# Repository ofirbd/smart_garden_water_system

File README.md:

# Smart Garden Water System

## Project Overview

This repository contains the software and hardware design for a smart garden system designed to automate watering, monitor water consumption, and track environmental conditions (temperature and humidity). The system leverages an ESP32 microcontroller for edge device control and a Raspberry Pi as a central hub, all controllable via a dedicated mobile application.

Built upon prior experience with ESP32 and MQTT, this project aims to create a robust, scalable, and user-friendly solution for efficient garden management.

## Key Features

* **Automated Watering:** Schedule-based watering for up to 3 individual garden zones.
* **Manual Control:** On-demand opening and closing of each water valve via the mobile app.
* **Water Usage Monitoring:** Real-time and historical tracking of total and session water consumption from a single water meter.
* **Environmental Monitoring:** Live readings and historical data for garden temperature and humidity.
* **System Status:** Real-time feedback on valve states, device connectivity, and battery levels.
* **Notifications:** Alerts for critical events (e.g., low battery, potential issues).
* **User-Friendly Mobile App:** Intuitive interface for control, monitoring, and configuration.

## System Architecture

The system follows a star-topology with a central Raspberry Pi hub communicating with a single, powerful ESP32 edge device.

```
+-------------------+             +-----------------------+
|                   |             |                       |
| Mobile Application| <---------> | Central Control Unit  |
| (Android/iOS)     | (MQTT/HTTP) | (Raspberry Pi)        |
|                   |             | - MQTT Broker         |
+-------------------+             | - Data Storage        |
| - API/Web Server      |
+-----------+-----------+
|
| MQTT
|
+-----------+-----------+
|                       |
| Combined Smart Water  |
| Unit (ESP32)          |
| - 3x Valve Actuation  |
| - 1x Water Flow Sensor|
| - Temp/Hum Sensors    |
| - Status Reporting    |
| - Data Reporting      |
| - Battery/Power       |
+-----------------------+
```

## Components

### 1. Combined Smart Water Unit (ESP32 Firmware & Hardware)

This single ESP32 board manages all direct interactions with the garden.

* **Microcontroller:** ESP32 (e.g., ESP32-WROOM-32 or similar, ensuring sufficient GPIOs).
* **Valve Actuators:** 3 x Latching Solenoid Valves (recommended for their minimal power consumption) with appropriate driver circuits (e.g., MOSFET H-bridge for polarity switching).
* **Water Flow Sensor:** 1 x Hall-effect flow sensor (e.g., YF-S201C or equivalent), connected to an interrupt-capable GPIO.
* **Temperature/Humidity Sensor:** [Specify your chosen sensor, e.g., BME280 (I2C) or DHT22 (1-wire)].
* **Power Supply:** Designed for outdoor deployment, likely battery-powered (e.g., 18650 Li-ion cells) with a robust charging circuit (e.g., solar panel + charge controller) and efficient voltage regulation. Alternatively, mains power if available.
* **Enclosure:** IP65/IP67 rated waterproof enclosure to protect electronics from elements.
* **Firmware:** Developed in C++ using the [ESP-IDF framework / Arduino IDE].

### 2. Central Control Unit (Raspberry Pi Software & Hardware)

The brain of the system, handling data, scheduling, and communication with the mobile app.

* **Hardware:** Raspberry Pi [Specify model, e.g., 3B+, 4, or 5].
* **Operating System:** Raspberry Pi OS (formerly Raspbian).
* **MQTT Broker:** Mosquitto (for reliable message queuing between devices).
* **Database:** SQLite (chosen for its lightweight nature, ease of setup, and suitability for the project's data scale).
    * Stores sensor readings, valve states, schedules, and device information.
* **Backend Application/API:** A custom application written in [Python (e.g., Flask/FastAPI), Node.js (e.g., Express), or Go].
    * Listens to MQTT messages, stores data in SQLite, implements scheduling logic, and exposes a RESTful API for the mobile application.
* **Web Tool (Optional but Recommended):** [Specify your chosen tool, e.g., Home Assistant, Node-RED, or ThingsBoard].
    * Provides a ready-made web interface for dashboards, charts, and rule-based automation, significantly reducing development time for the UI.

### 3. Mobile Application

The primary user interface for controlling and monitoring the garden from anywhere.

* **Platform:** Compatible with Android and/or iOS devices.
* **Technology Stack:** [Specify, e.g., React Native, Flutter, Native Kotlin/Swift].
* **Functionality:**
    * Dashboard view with current status and summarized data.
    * Individual valve control (on/off).
    * Display of current and historical water meter readings.
    * Display of current and historical temperature and humidity data.
    * Creation, editing, and deletion of watering schedules per valve.
    * System configuration settings.

## Detailed System Description and Requirements

For an in-depth understanding of the system's complete architecture, detailed hardware and software requirements for each component, precise communication protocols, and in-depth design considerations, please refer to the dedicated **[system_requirements.md](./01-docs/system_requirements.md)** and  **[system_detailed_design.md](./01-docs/system_detailed_design.md)** documents. These comprehensive documents also outlines potential future enhancements and specific implementation details.

## Setup & Installation

Follow these steps to get your Smart Garden Water System up and running:

### 1. Raspberry Pi (Central Control Unit) Setup

1.  **Prepare Raspberry Pi OS:**
    * Download and flash the latest Raspberry Pi OS (Lite or Desktop, depending on your preference) onto a microSD card using [Raspberry Pi Imager](https://www.raspberrypi.com/software/).
    * Enable SSH for remote access.
2.  **Install Mosquitto MQTT Broker:**
    
    ```bash
    sudo apt update
    sudo apt install mosquitto mosquitto-clients
    sudo systemctl enable mosquitto
    sudo systemctl start mosquitto
    # For security, consider configuring MQTT users and passwords (refer to Mosquitto docs).
    ```
3.  **Setup Backend Application / Web Tool:**
    * **If using a custom backend:**
        ```bash
        git clone [Your_Repository_URL]
        cd [Your_Repository_Name]/backend/
        # Install Python dependencies (example for Python)
        pip install -r requirements.txt
        # Run the backend application (e.g., using Gunicorn for production)
        python app.py
        ```
    * **If using Home Assistant:** Follow the official installation guide (e.g., Home Assistant OS, Container, or Supervised for Raspberry Pi). Ensure MQTT integration is configured to connect to your Mosquitto broker.
    * **If using Node-RED:** Install via the recommended script for Raspberry Pi: `bash <(curl -sL https://raw.githubusercontent.com/node-red/linux-installers/master/deb/update-nodejs-and-nodered)` Then install necessary nodes (e.g., `node-red-contrib-mqtt`, `node-red-node-sqlite`).
    * **If using ThingsBoard:** Follow the official ThingsBoard Community Edition installation guide for Raspberry Pi (Docker is often the easiest).

### 2. ESP32 (Smart Water Unit) Firmware

1.  **Set up Development Environment:**
    * Install either [ESP-IDF](https://docs.espressif.com/projects/esp-idf/en/latest/esp32/get-started/index.html) or [Arduino IDE with ESP32 board support](https://docs.espressif.com/projects/arduino-esp32/en/latest/installing.html).
2.  **Clone Firmware Repository:**
    ```bash
    git clone [Your_Repository_URL]
    cd [Your_Repository_Name]/esp32_firmware/
    ```
3.  **Configure Network & MQTT:**
    * Open the firmware project in your IDE.
    * Locate and edit the configuration file (e.g., `src/config.h`, `secrets.h`, or similar) to enter your Wi-Fi SSID, password, and the IP address/hostname of your Raspberry Pi's MQTT broker.
4.  **Compile and Upload:**
    * Compile the firmware and upload it to your ESP32 board. Ensure correct board and serial port are selected in your IDE.

### 3. Mobile Application

1.  **Clone Mobile App Repository:**
    ```bash
    git clone [Your_Mobile_App_Repository_URL]
    cd [Your_Mobile_App_Repository_Name]
    ```
2.  **Install Dependencies:**
    * For React Native: `npm install` or `yarn install`
    * For Flutter: `flutter pub get`
    * Follow specific instructions for your chosen framework.
3.  **Configure API Endpoint:**
    * In the app's source code, update the backend API base URL to point to your Raspberry Pi's IP address (e.g., `http://[Raspberry_Pi_IP_Address]:[Backend_Port]`).
4.  **Build and Run:**
    * Run the app on an emulator or a physical device:
        * React Native: `npm run android` / `npm run ios`
        * Flutter: `flutter run`
    * Alternatively, build release APK/IPA files for direct installation.

## Usage

1.  **Power On Devices:** Ensure your Raspberry Pi and the ESP32 Smart Water Unit are powered on and connected to your local network.
2.  **Verify MQTT Communication:** Monitor the Mosquitto broker logs (`sudo tail -f /var/log/mosquitto/mosquitto.log`) to confirm the ESP32 is publishing data and subscribing correctly.
3.  **Access Interface:**
    * **Mobile App:** Launch the "Smart Garden Water System" app on your smartphone.
    * **Web Tool:** Open your web browser and navigate to `http://[Raspberry_Pi_IP_Address]:[Web_Tool_Port]` (e.g., `http://192.168.1.100:8123` for Home Assistant, `http://192.168.1.100:1880` for Node-RED, `http://192.168.1.100:8080` for ThingsBoard).
4.  **Control & Monitor:**
    * Use the interface to manually open or close individual water valves.
    * View real-time and historical graphs for water flow, total volume, temperature, and humidity.
    * Create and manage custom watering schedules for your garden zones.
    * Check the battery status and overall health of your ESP32 unit.

## License

This project is open-source and distributed under the MIT License. See the `LICENSE` file for more details.

---

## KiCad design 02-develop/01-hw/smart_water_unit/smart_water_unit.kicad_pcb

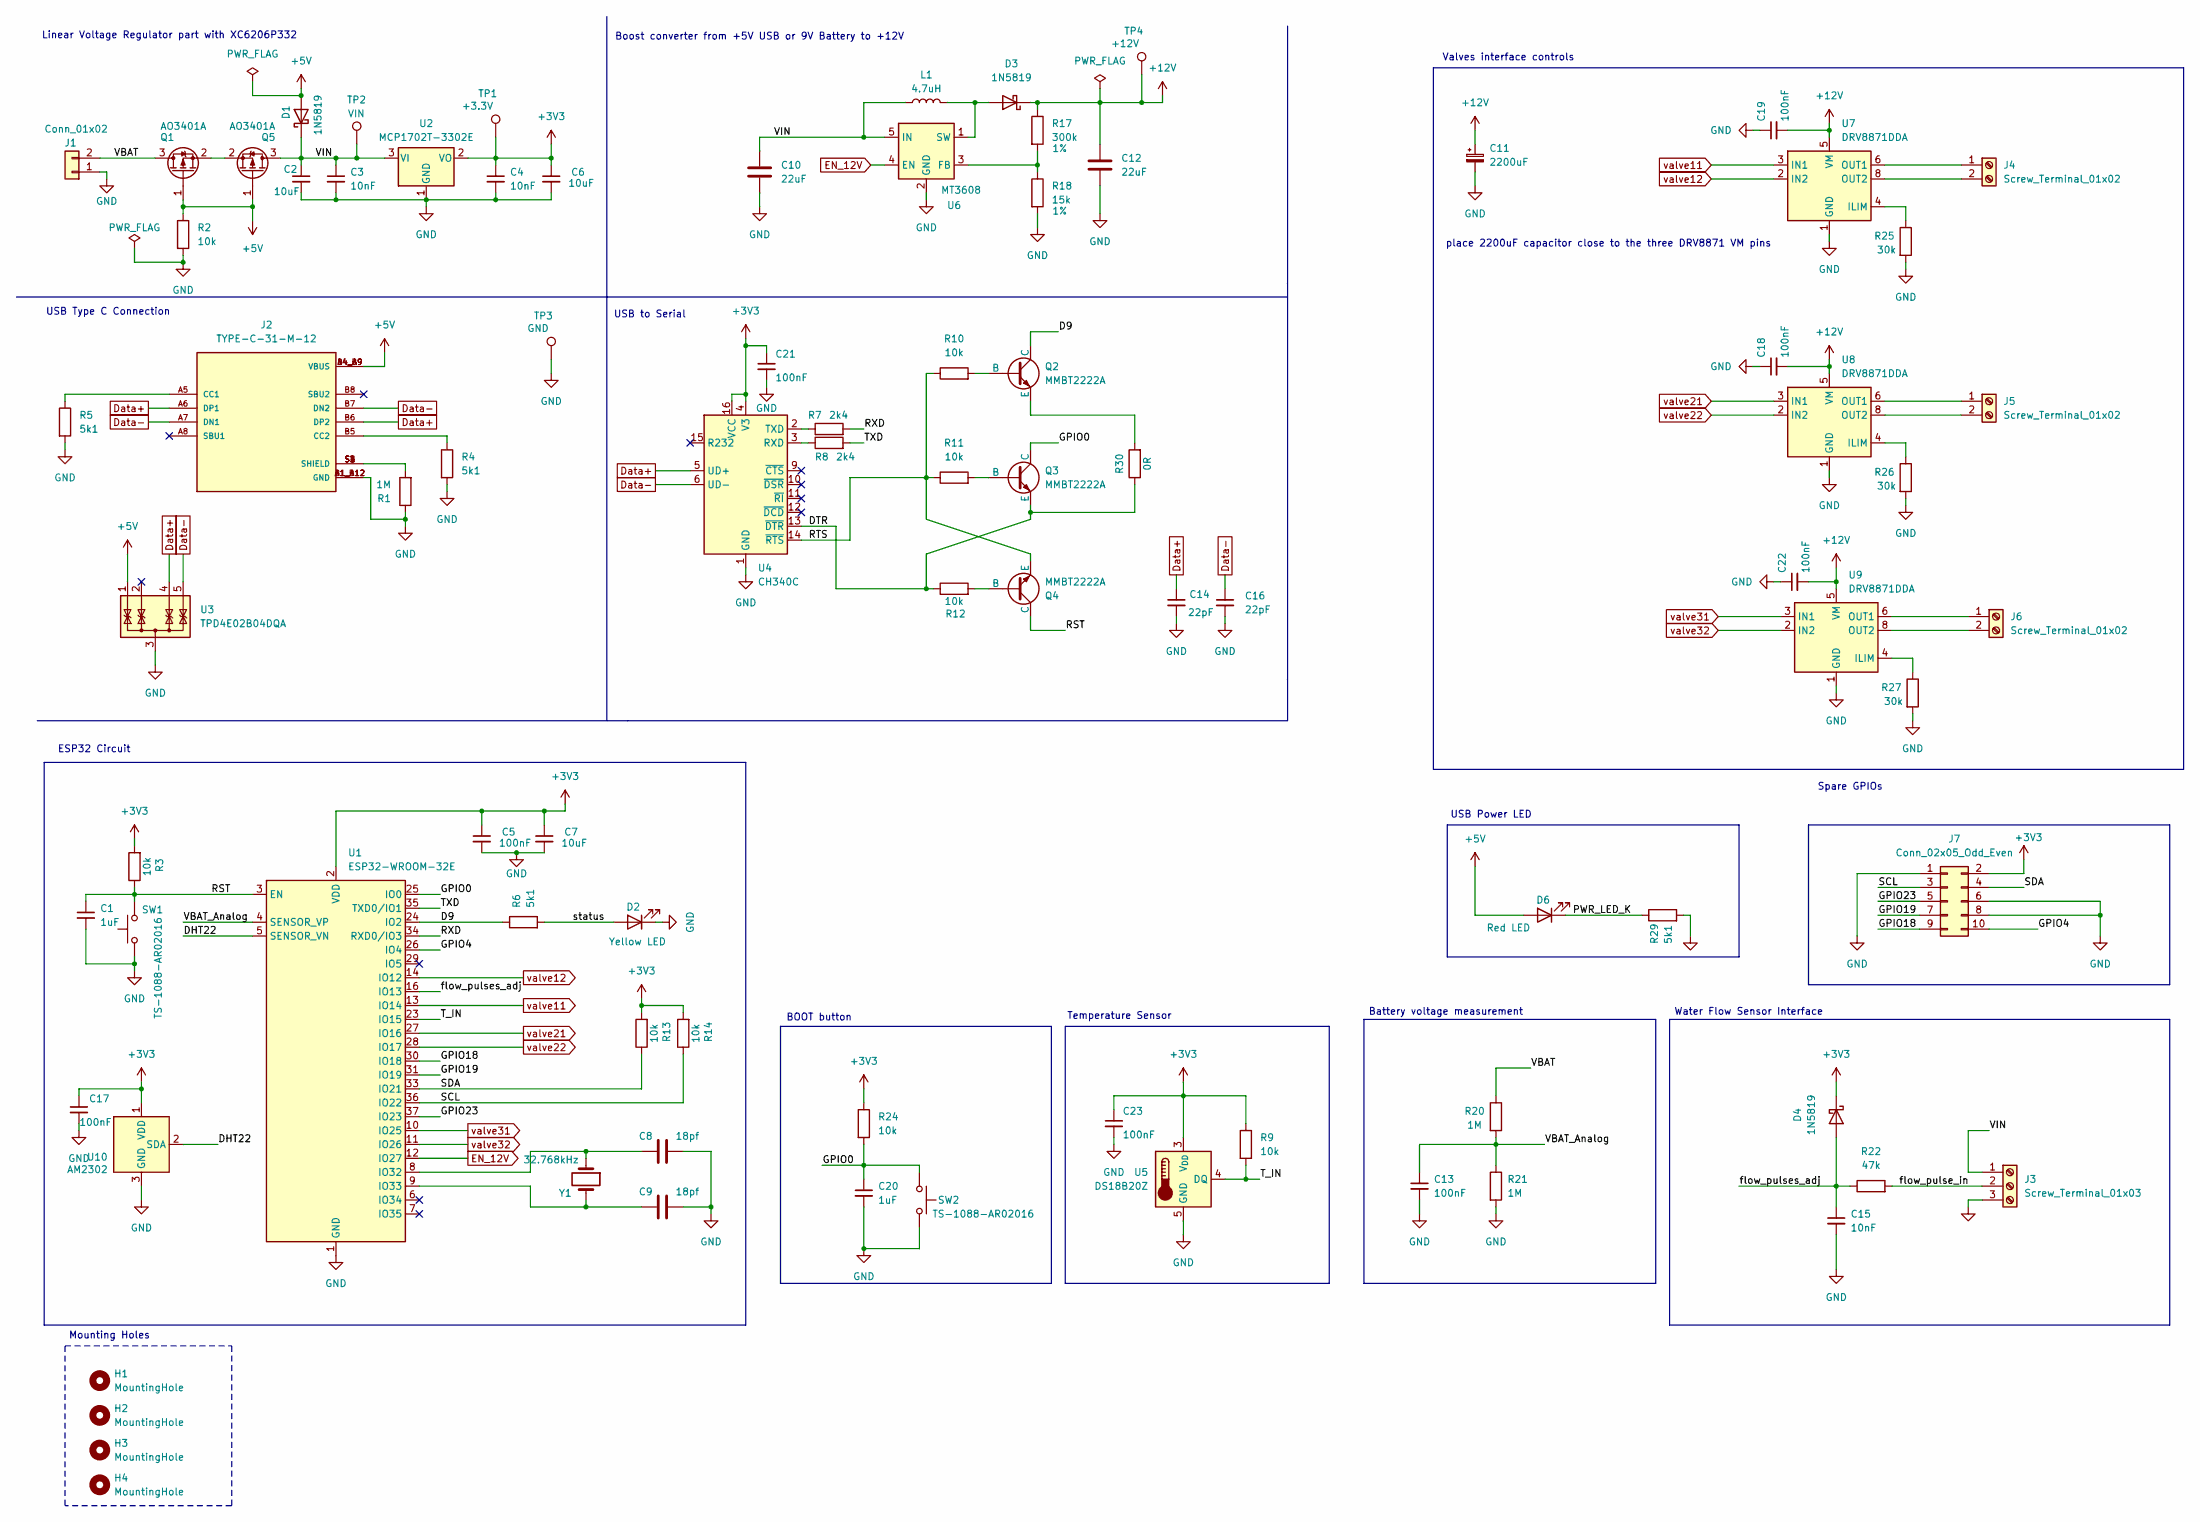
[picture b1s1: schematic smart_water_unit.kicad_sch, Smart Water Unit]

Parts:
C1, C20: 1uF; C_0603_1608Metric; LCSC C15849
C2, C6: 10uF; C_0805_2012Metric; MPN CL21A106KAYNNNE; LCSC C15850
C3, C4, C15: 10nF; C_0603_1608Metric; LCSC C57112
C5, C13, C17, C18, C19, C21, C22, C23: 100nF; C_0603_1608Metric; LCSC C14663
C7: 10uF; C_0603_1608Metric; LCSC C96446
C8, C9: 18pf; C_0603_1608Metric; MPN CL10C180JB8NNNC; LCSC C1647
C10, C12: 22uF; C_1206_3216Metric; MPN CL31A226KAHNNNE; LCSC C12891
C11: 2200uF; C_TH_Horizontal_P5_13x22mm
C14, C16: 22pF; C_0603_1608Metric; LCSC C1653
D1, D3, D4: 1N5819; D_SOD-123; MPN B5819W SL; LCSC C8598
D2: Yellow LED; LED_0603_1608Metric; LCSC C2296
D6: Red LED; LED_0603_1608Metric; LCSC C2286
H1, H2, H3, H4: MountingHole; MountingHole_2.2mm_M2
J1: Conn_01x02; PinHeader_1x02_P2.54mm_Vertical
J2: TYPE-C-31-M-12; HRO_TYPE-C-31-M-12; PARTREV 2020.12.08; LCSC C165948
J3: Screw_Terminal_01x03; TerminalBlock_Phoenix_MKDS-1,5-3-5.08_1x03_P5.08mm_Horizont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
J4, J5, J6: Screw_Terminal_01x02; TerminalBlock_Phoenix_MKDS-1,5-2-5.08_1x02_P5.08mm_Horizont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
J7: Conn_02x05_Odd_Even; PinHeader_2x05_P2.54mm_Vertical
L1: 4.7uH; L_APV_ANR4018; MPN SPH4018H4R7MT; LCSC C98400
Q1, Q5: AO3401A; SOT-23; LCSC C10487
Q2, Q3, Q4: MMBT2222A; SOT-23; LCSC C8512
R1, R20, R21: 1M; R_0603_1608Metric; LCSC C22935
R2, R3, R9, R10, R11, R12, R13, R14, R24: 10k; R_0603_1608Metric; LCSC C25804
R4, R5, R6, R29: 5k1; R_0603_1608Metric; LCSC C23186
R7, R8: 2k4; R_0603_1608Metric; LCSC C22940
R17: 300k; R_0603_1608Metric; MPN 0603WAF3003T5E; LCSC C23024
R18: 15k; R_0603_1608Metric; LCSC C22809
R22: 47k; R_0603_1608Metric; LCSC C25819
R25, R26, R27: 30k; R_0603_1608Metric; MPN 0603WAF3002T5E; LCSC C22984
R30: 0R; R_0603_1608Metric; LCSC C21189
SW1, SW2: TS-1088-AR02016; SW_Push_SPST_SMD_5mmx3mm; MPN TS-1088-AR02016; LCSC C720477
TP1: +3.3V; TestPoint_THTPad_D2.0mm_Drill1.0mm
TP2: VIN; TestPoint_THTPad_D2.0mm_Drill1.0mm
TP3: GND; TestPoint_THTPad_2.5x2.5mm_Drill1.2mm
TP4: +12V; TestPoint_THTPad_D2.0mm_Drill1.0mm
U1: ESP32-WROOM-32E; MPN ESP32-WROOM-32D-N16; LCSC C529578
U2: MCP1702T-3302E; SOT-89-3; LCSC C88418
U3: TPD4E02B04DQA; USON-10_2.5x1.0mm_P0.5mm; LCSC C1973193
U4: CH340C; SOIC-16_3.9x9.9mm_P1.27mm; LCSC C84681
U5: DS18B20Z; SOIC-8_5.3x6.2mm_P1.27mm; MPN MY18B20Z; LCSC C5261093
U6: MT3608; SOT-23-6; LCSC C84817
U7, U8, U9: DRV8871DDA; Texas_HTSOP-8-1EP_3.9x4.9mm_P1.27mm_EP2.95x4.9mm_Mask2.4x3.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; MPN DRV8871DDAR; LCSC C75864
U10: AM2302; ASAIR_AM2302_P2.54mm_Vertical
Y1: 32.768kHz; Crystal_C38-LF_D3.0mm_L8.0mm_Horizontal

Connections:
+3V3: C4.1, C5.1, C6.1, C7.1, C17.1, C21.1, C23.1, D4.1 (K), J7.2, R3.2, R9.1, R13.2, R14.2, R24.1, TP1.1, U1.2 (VDD), U2.2 (VO), U4.4 (V3), U4.16 (VCC), U5.3 (V_{DD}), U10.1 (VDD)
+5V: D1.2 (A), D6.2 (A), J2.A4_B9 (VBUS), J2.B4_A9 (VBUS), Q1.1 (G), Q5.1 (G), R2.1, U3.1 (IO1)
+12V: C11.1, C12.1, C18.2, C19.2, C22.2, D3.1 (K), R17.1, TP4.1, U7.5 (VM), U8.5 (VM), U9.5 (VM)
/D9: Q2.1 (C), R6.1, U1.24 (IO2)
/DHT22: U1.5 (SENSOR_VN), U10.2 (SDA)
/DTR: Q3.3 (E), R12.1, R30.1, U4.13 (~DTR)
/GPIO0: C20.1, Q3.1 (C), R24.2, SW2.1, U1.25 (IO0)
/GPIO4: J7.10, U1.26 (IO4)
/GPIO18: J7.9, U1.30 (IO18)
/GPIO19: J7.7, U1.31 (IO19)
/GPIO23: J7.5, U1.37 (IO23)
/PWR_LED_K: D6.1 (K), R29.1
/RST: C1.1, Q4.1 (C), R3.1, SW1.2, U1.3 (EN)
/RTS: Q4.3 (E), R10.1, R11.1, U4.14 (~RTS)
/RXD: R7.2, U1.34 (RXD0/IO3)
/SCL: J7.3, R14.1, U1.36 (IO22)
/SDA: J7.4, R13.1, U1.33 (IO21)
/TXD: R8.2, U1.35 (TXD0/IO1)
/T_IN: R9.2, U1.23 (IO15), U5.4 (DQ)
/VBAT: J1.2, Q1.3 (D), R20.1
/VBAT_Analog: C13.1, R20.2, R21.1, U1.4 (SENSOR_VP)
/VIN: C2.1, C3.1, C10.1, D1.1 (K), J3.1, L1.1, Q5.3 (D), TP2.1, U2.3 (VI), U6.5 (IN)
/flow_pulse_in: J3.2, R22.2
/flow_pulses_adj: C15.1, D4.2 (A), R22.1, U1.16 (IO13)
/status: D2.2 (A), R6.2
Data+: C14.1, J2.A6 (DP1), J2.B6 (DP2), U3.4 (IO3), U4.5 (UD+)
Data-: C16.1, J2.A7 (DN1), J2.B7 (DN2), U3.5 (IO4), U4.6 (UD-)
EN_12V: U1.12 (IO27), U6.4 (EN)
GND: C1.2, C2.2, C3.2, C4.2, C5.2, C6.2, C7.2, C8.2, C9.2, C10.2, C11.2, C12.2, C13.2, C14.2, C15.2, C16.2, C17.2, C18.1, C19.1, C20.2, C21.2, C22.1, C23.2, D2.1 (K), J1.1, J2.A1_B12 (GND), J2.B1_A12 (GND), J3.3, J7.1, J7.6, J7.8, R1.1, R2.2, R4.2, R5.2, R18.2, R21.2, R25.2, R26.2, R27.2, R29.2, SW1.1, SW2.2, TP3.1, U1.1 (GND), U1.15 (GND), U1.38 (GND), U1.39 (GND), U2.1 (GND), U3.3 (G), U3.8 (G), U4.1 (GND), U5.5 (GND), U6.2 (GND), U7.1 (GND), U7.7 (GND), U7.9 (GND), U8.1 (GND), U8.7 (GND), U8.9 (GND), U9.1 (GND), U9.7 (GND), U9.9 (GND), U10.3 (GND), U10.4 (GND)
unnamed: D3.2 (A), L1.2, U6.1 (SW)
unnamed: J2.A5 (CC1), R5.1
unnamed: J2.B5 (CC2), R4.1
unnamed: J2.S1 (SHIELD), J2.S2 (SHIELD), J2.S3 (SHIELD), J2.S4 (SHIELD), R1.2
unnamed: J4.1, U7.6 (OUT1)
unnamed: J4.2, U7.8 (OUT2)
unnamed: J5.1, U8.6 (OUT1)
unnamed: J5.2, U8.8 (OUT2)
unnamed: J6.1, U9.6 (OUT1)
unnamed: J6.2, U9.8 (OUT2)
unnamed: Q1.2 (S), Q5.2 (S)
unnamed: Q2.2 (B), R10.2
unnamed: Q2.3 (E), R30.2
unnamed: Q3.2 (B), R11.2
unnamed: Q4.2 (B), R12.2
unnamed: C8.1, U1.8 (IO32), Y1.1
unnamed: C9.1, U1.9 (IO33), Y1.2
unnamed: R8.1, U4.3 (RXD)
unnamed: R7.1, U4.2 (TXD)
unnamed: R17.2, R18.1, U6.3 (FB)
unnamed: R25.1, U7.4 (ILIM)
unnamed: R26.1, U8.4 (ILIM)
unnamed: R27.1, U9.4 (ILIM)
valve11: U1.13 (IO14), U7.3 (IN1)
valve12: U1.14 (IO12), U7.2 (IN2)
valve21: U1.27 (IO16), U8.3 (IN1)
valve22: U1.28 (IO17), U8.2 (IN2)
valve31: U1.10 (IO25), U9.3 (IN1)
valve32: U1.11 (IO26), U9.2 (IN2)

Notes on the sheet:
Linear Voltage Regulator part with XC6206P332
BOOT button
Water Flow Sensor Interface
USB Type C Connection
Boost converter from +5V USB or 9V Battery to +12V
ESP32 Circuit
place 2200uF capacitor close to the three DRV8871 VM pins
Mounting Holes
USB to Serial
Spare GPIOs
Valves interface controls
Temperature Sensor
USB Power LED
Battery voltage measurement

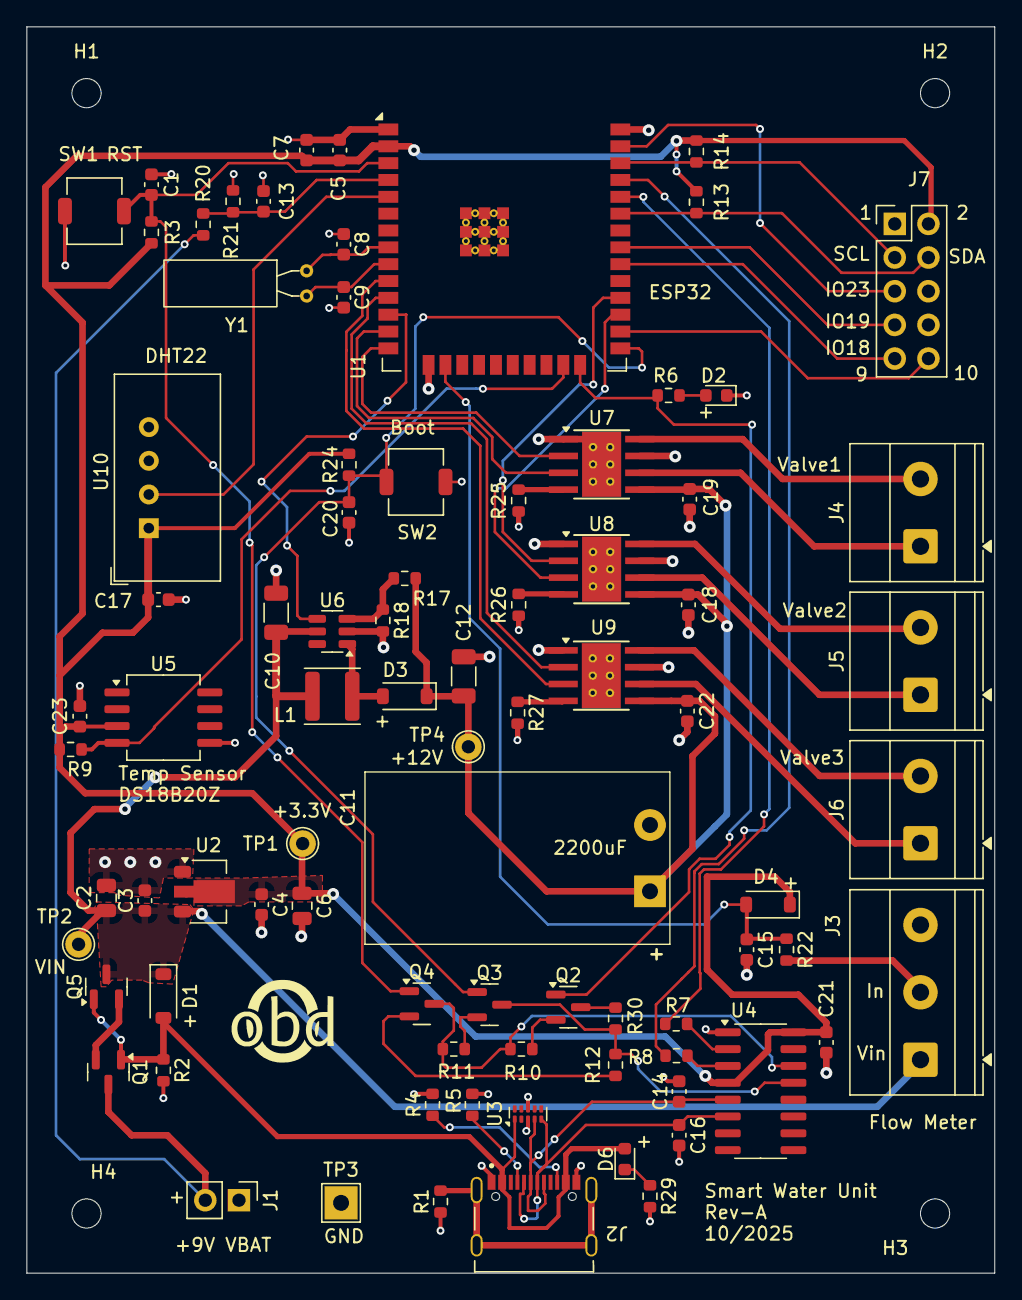
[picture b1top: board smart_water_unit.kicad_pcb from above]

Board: 2 copper layers, 73.0 x 94.0 mm, 87 parts (0 on the bottom side), 58 nets.

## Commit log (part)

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2025-07-04 this is the first working firmware on esp32 with support for valves scheduling
2025-07-04 added web application with backend and frontend
2025-07-05 added mobile web app
2025-07-05 added mobile_web_app_design screenshots
2025-07-05 updated docs
2025-07-11 changed ip address of the Raspberry PI to run the web app in its IP and not localhost
2025-07-11 removed the RPI IP address and set it as a parameter
2025-07-13 added smart-garden-backend.service to operate the backend service process as a service on the Raspberry pi and update the documentation
2025-08-16 hardware design started
2025-08-16 updated hardware folder
2025-09-13 updated hardware development KiCAD
2025-10-11 hw schematic complete, pcb placement and most routing
2025-11-22 hardware pcb v1 sent to production
2025-11-22 updated firmware to align with hardware and updated the docs
2025-12-13 adding development board tests
2026-01-03 updated without temperature sensor and added two batch files - dev board and production board
